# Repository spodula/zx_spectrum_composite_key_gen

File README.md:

# zx_spectrum_composite_key_gen
zx Spectrum composite key generator PCB. 

This PCB goes in parallel with the normal keyboard tails and allows composite keys to be wired to their own seperate keys with a seperate header for the cursor keys. 

Bugs: 
Left diodes are backwards to the rest. Silk screen is correct. Be careful assembling

Corrected bugs:
U4 is the wrong way around
Most of the symbol shift chars are not linked to to symbol shift. Whoops.

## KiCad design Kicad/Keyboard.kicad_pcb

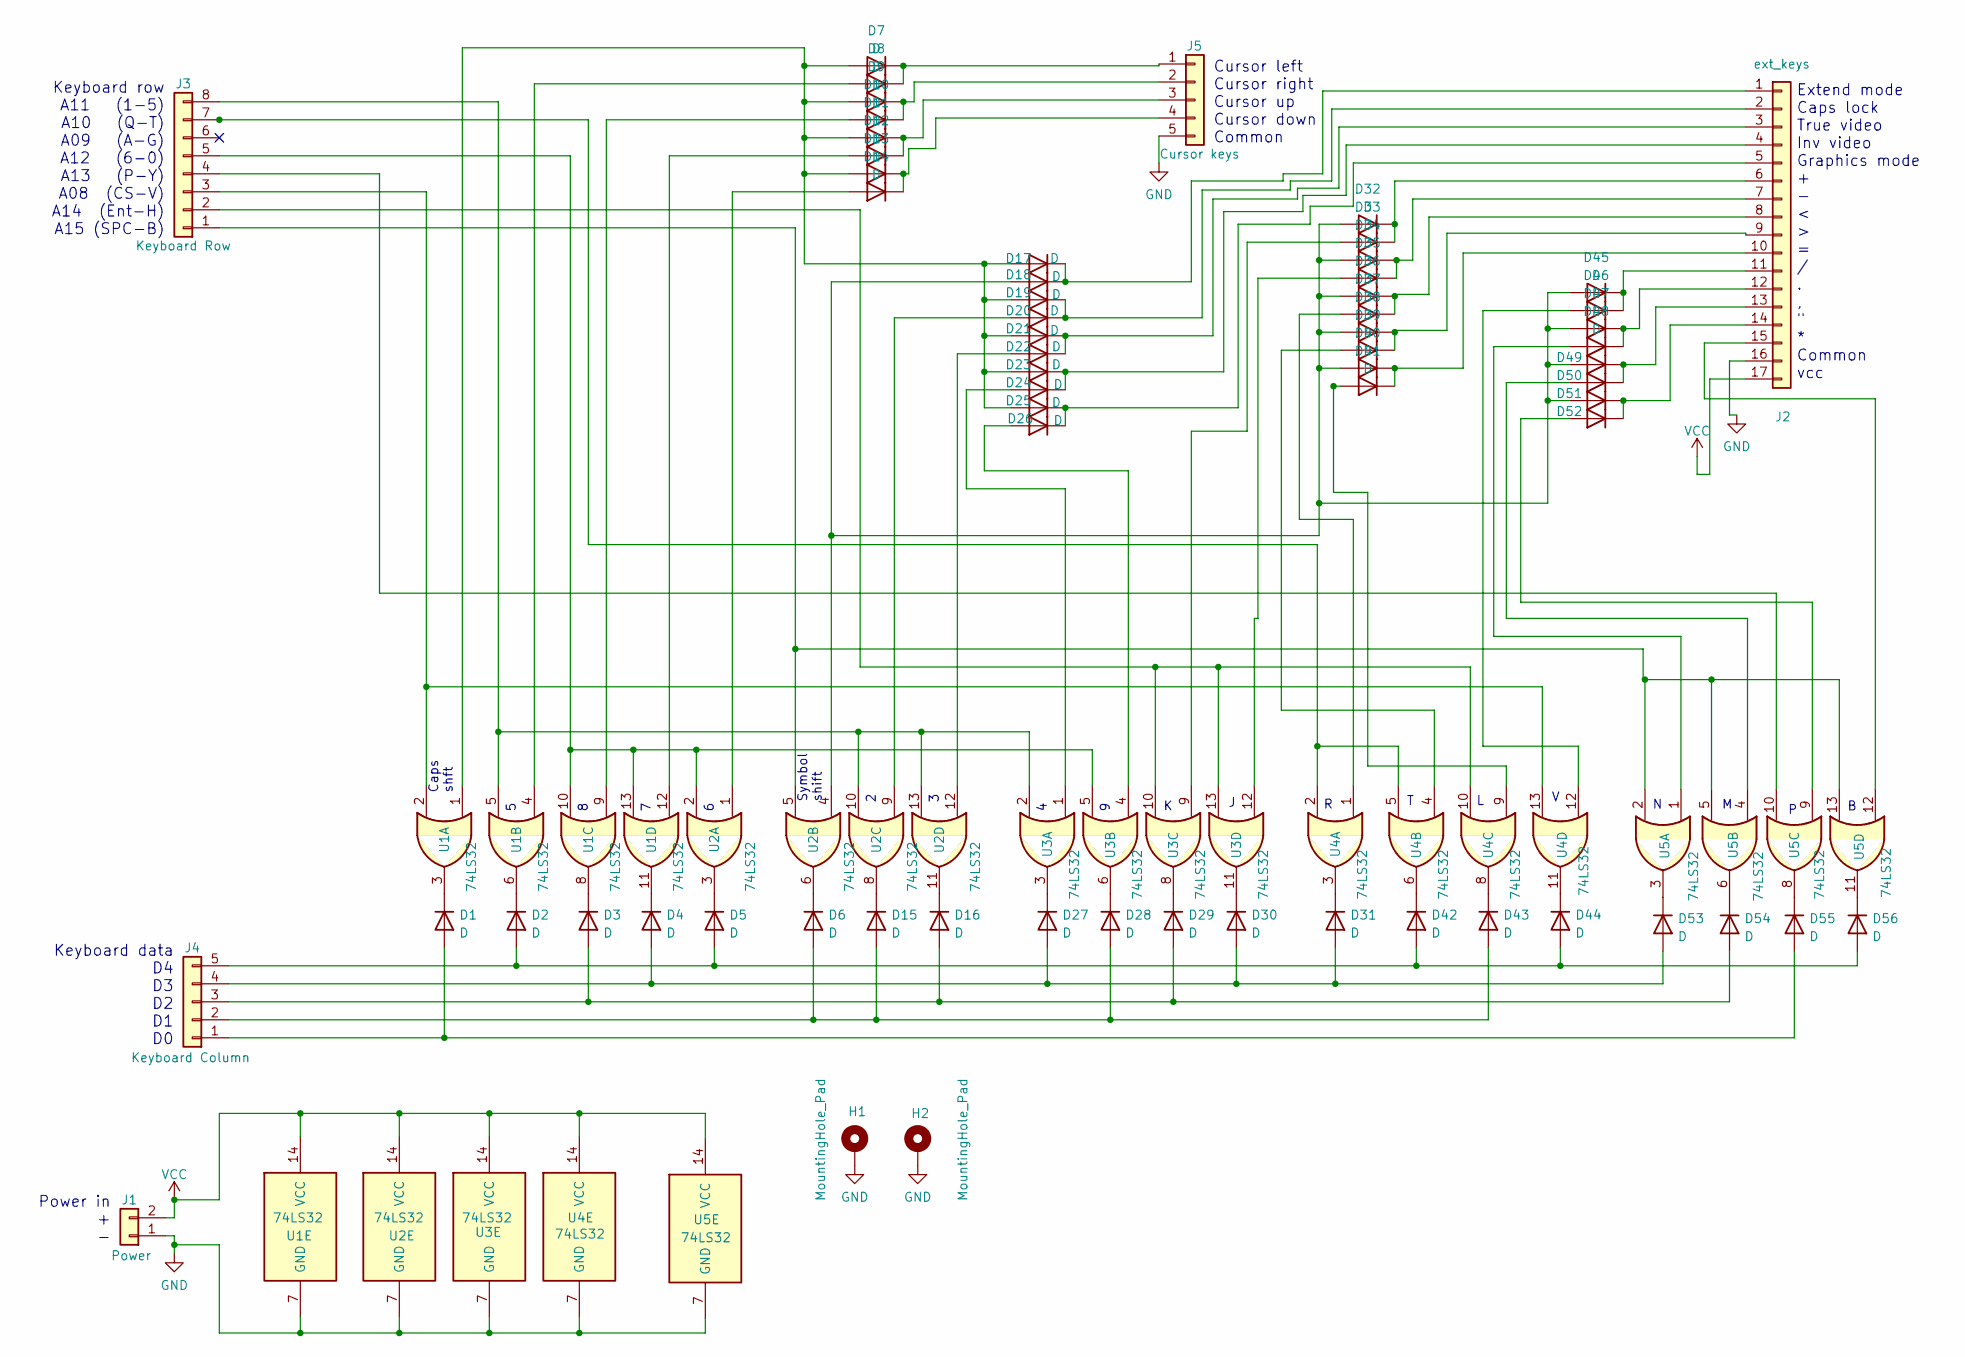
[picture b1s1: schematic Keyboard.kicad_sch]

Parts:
D1, D2, D3, D4, D5, D6, D7, D8, D9, D10, D11, D12, D13, D14, D15, D16, D17, D18, D19, D20, D21, D22, D23, D24, D25, D26, D27, D28, D29, D30, D31, D32, D33, D34, D35, D36, D37, D38, D39, D40, D41, D42, D43, D44, D45, D46, D47, D48, D49, D50, D51, D52, D53, D54, D55, D56: D; D_A-405_P7.62mm_Horizontal
H1, H2: MountingHole_Pad; MountingHole_3.5mm_Pad
J1: Power; PinSocket_1x02_P2.54mm_Horizontal
J2: ext_keys; PinSocket_1x17_P2.54mm_Horizontal
J3: Keyboard Row; PinSocket_1x08_P2.54mm_Horizontal
J4: Keyboard Column; PinSocket_1x05_P2.54mm_Horizontal
J5: Cursor keys; PinSocket_1x05_P2.54mm_Horizontal
U1, U2, U3, U4, U5: 74LS32; DIP-14_W7.62mm_LongPads

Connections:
GND: H1.1, H2.1, J1.1, J2.16, J5.5, U1.7 (GND), U2.7 (GND), U3.7 (GND), U4.7 (GND), U5.7 (GND)
unnamed: D1.1 (K), U1.3
unnamed: D1.2 (A), D55.2 (A), J4.1
unnamed: D2.1 (K), U1.6
unnamed: D2.2 (A), D5.2 (A), D42.2 (A), D44.2 (A), D56.2 (A), J4.5
unnamed: D3.1 (K), U1.8
unnamed: D4.1 (K), U1.11
unnamed: D5.1 (K), U2.3
unnamed: D6.1 (K), U2.6
unnamed: D7.1 (K), D8.1 (K), J5.1
unnamed: D8.2 (A), U1.4
unnamed: D9.1 (K), D10.1 (K), J5.2
unnamed: D10.2 (A), U1.9
unnamed: D11.1 (K), D12.1 (K), J5.3
unnamed: D7.2 (A), D9.2 (A), D11.2 (A), D13.2 (A), D17.2 (A), D19.2 (A), D21.2 (A), D23.2 (A), D25.2 (A), U1.1
unnamed: D12.2 (A), U1.12
unnamed: D13.1 (K), D14.1 (K), J5.4
unnamed: D14.2 (A), U2.1
unnamed: D15.1 (K), U2.8
unnamed: D6.2 (A), D15.2 (A), D28.2 (A), D43.2 (A), J4.2
unnamed: D16.1 (K), U2.11
unnamed: D3.2 (A), D16.2 (A), D29.2 (A), D54.2 (A), J4.3
unnamed: D17.1 (K), D18.1 (K), J2.1
unnamed: D18.2 (A), D32.2 (A), D34.2 (A), D36.2 (A), D38.2 (A), D40.2 (A), D45.2 (A), D47.2 (A), D49.2 (A), D51.2 (A), U2.4
unnamed: D19.1 (K), D20.1 (K), J2.2
unnamed: D20.2 (A), U2.9
unnamed: D21.1 (K), D22.1 (K), J2.3
unnamed: D22.2 (A), U2.12
unnamed: D23.1 (K), D24.1 (K), J2.4
unnamed: D24.2 (A), U3.1
unnamed: D25.1 (K), D26.1 (K), J2.5
unnamed: D26.2 (A), U3.4
unnamed: D27.1 (K), U3.3
unnamed: D4.2 (A), D27.2 (A), D30.2 (A), D31.2 (A), D53.2 (A), J4.4
unnamed: D28.1 (K), U3.6
unnamed: D29.1 (K), U3.8
unnamed: D30.1 (K), U3.11
unnamed: D31.1 (K), U4.3
unnamed: D32.1 (K), D33.1 (K), J2.6
unnamed: D33.2 (A), U3.9
unnamed: D34.1 (K), D35.1 (K), J2.7
unnamed: D35.2 (A), U3.12
unnamed: D36.1 (K), D37.1 (K), J2.8
unnamed: D37.2 (A), U4.1
unnamed: D38.1 (K), D39.1 (K), J2.9
unnamed: D39.2 (A), U4.4
unnamed: D40.1 (K), D41.1 (K), J2.10
unnamed: D41.2 (A), U4.9
unnamed: D42.1 (K), U4.6
unnamed: D43.1 (K), U4.8
unnamed: D44.1 (K), U4.11
unnamed: D45.1 (K), D46.1 (K), J2.11
unnamed: D46.2 (A), U4.12
unnamed: D47.1 (K), D48.1 (K), J2.12
unnamed: D48.2 (A), U5.1
unnamed: D49.1 (K), D50.1 (K), J2.13
unnamed: D50.2 (A), U5.4
unnamed: D51.1 (K), D52.1 (K), J2.14
unnamed: D52.2 (A), U5.9
unnamed: D53.1 (K), U5.3
unnamed: D54.1 (K), U5.6
unnamed: D55.1 (K), U5.8
unnamed: D56.1 (K), U5.11
unnamed: J2.15, U5.12
unnamed: J3.1, U2.5, U5.2, U5.5, U5.13
unnamed: J3.2, U3.10, U3.13, U4.10
unnamed: J3.3, U1.2, U4.13
unnamed: J3.4, U5.10
unnamed: J3.5, U1.10, U1.13, U2.2, U3.5
unnamed: J3.7, U4.2, U4.5
unnamed: J3.8, U1.5, U2.10, U2.13, U3.2
VCC: J1.2, J2.17, U1.14 (VCC), U2.14 (VCC), U3.14 (VCC), U4.14 (VCC), U5.14 (VCC)

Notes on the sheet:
Power in + -
Caps shft
Cursor left Cursor right Cursor up Cursor down Common
Extend mode Caps lock True video Inv video Graphics mode + - < > = / . , " * Common vcc
Symbol shift
Keyboard data D4 D3 D2 D1 D0
Keyboard row A11 (1-5) A10 (Q-T) A09 (A-G) A12 (6-0) A13 (P-Y) A08 (CS-V) A14 (Ent-H) A15 (SPC-B)

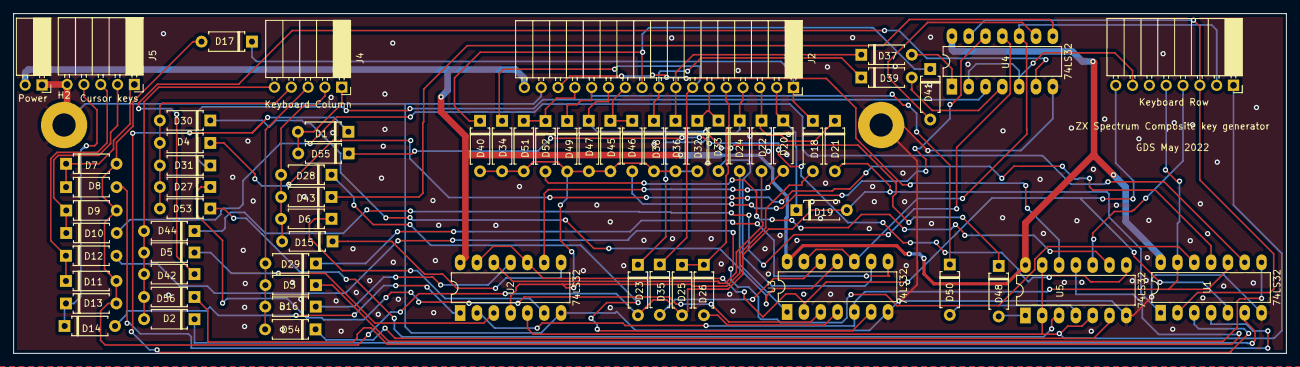
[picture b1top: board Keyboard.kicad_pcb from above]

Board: 2 copper layers, 192.2 x 51.3 mm, 68 parts (0 on the bottom side), 72 nets.

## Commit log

2022-06-22 shortened board, correction to link symbol shift to some chars, reversed U4 so it faces the same way as all the other ICs
